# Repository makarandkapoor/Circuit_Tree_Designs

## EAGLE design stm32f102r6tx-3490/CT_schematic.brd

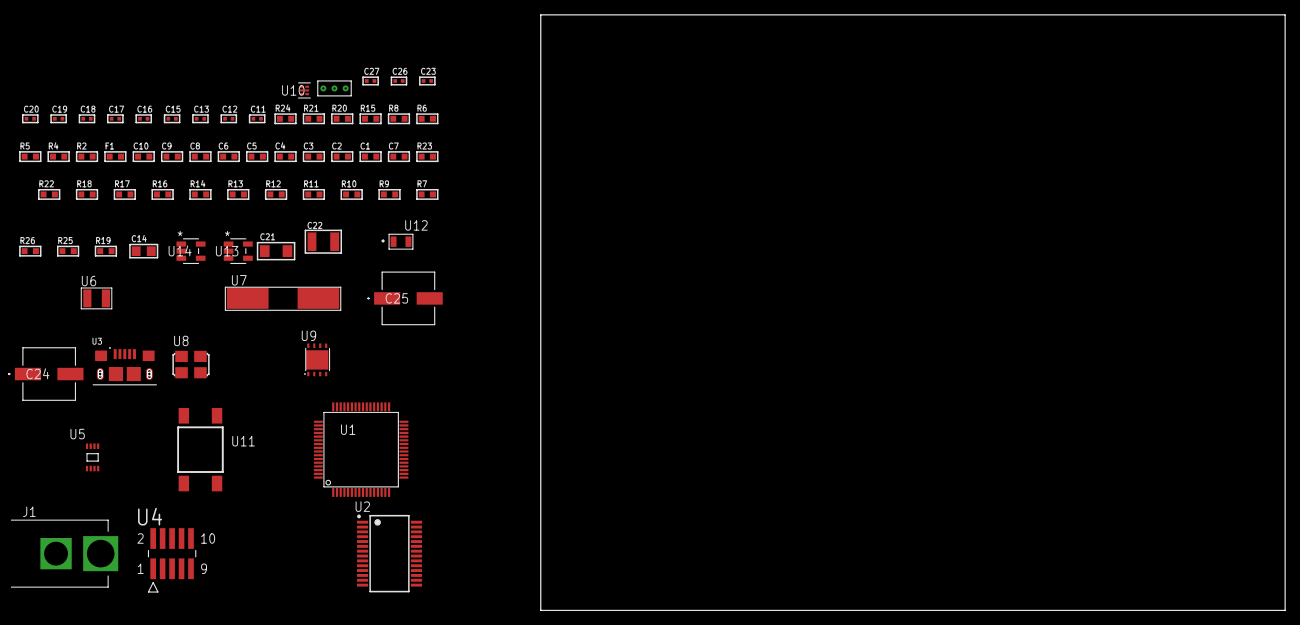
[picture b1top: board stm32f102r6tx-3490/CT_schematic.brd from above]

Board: 2 copper layers, 159.4 x 80.0 mm, 68 parts (0 on the bottom side), 42 nets, no tracks yet.

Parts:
C1, C10: 1e-06; C0603
C2, C3, C4, C5, C6: 1e-07; C0603
C7: 4.7e-06; C0603
C8, C9: 1e-08; C0603
C11, C12: 1e-11; C0402
C13, C15, C16, C17, C23: 1e-07; C0402
C14: 4.7e-06; C0805
C18, C19, C20, C26, C27: 1e-08; C0402
C21: 1e-05; C1206
C22: 1e-05; C1210
C24, C25: 0.0001; EXV-9H
F1: 240.0; L0603
J1: PJ-037B; PJ-037B_PACKAGE
R2, R21: 1000.0; R0603
R4, R8: 4700.0; R0603
R5, R6: 2200.0; R0603
R7, R9, R10, R11, R12, R13, R14, R16, R17, R18, R22, R23: 10000.0; R0603
R15: 5.0; R0603
R19: 100000.0; R0603
R20: 2231.0; R0603
R24: 9100.0; R0603
R25: 680000.0; R0603
R26: 120000.0; R0603
U1: STM32F102R6T6; LQFP64
U2: FT232RL-REEL; SSOP-28
U3: 10118193-0001LF; FCI_10118193-0001LF
U4: FTSH-105-01-L-DV-K; SAMTEC_FTSH-105-01-L-DV-K
U5: 24AA64T-I/MNY; TDFN-8/6MM
U6: ABS07-32.768KHZ-7-T
U7: ABLS-12.000MHZ-B4-T
U8: ASFL1-25MHZ-NCS; ASFL1
U9: LP3878SDX-ADJ/NOPB; WSON-8
U10: TPS3895ADRYR; SON-6
U11: 4-1437565-2; SW_4-1437565-2
U12: Q65110A2395; LGM67K-G1J2-24-Z
U13, U14: nc7sz125m5x; NC7SZ125M5X
U15: Dummy; DUMMY_PACKAGE_146

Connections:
CLK_CRYSTAL_U1_3: C11.1, U1.3, U6.1
CLK_CRYSTAL_U1_4: C12.1, U1.4, U6.2
CLK_CRYSTAL_U2_27: U2.27, U7.1
CLK_CRYSTAL_U2_28: U2.28, U7.2
CLK_U1_5: U1.5, U8.3
GND: C1.2, C2.2, C3.2, C4.2, C5.2, C6.2, C7.2, C8.2, C9.2, C10.2, C11.2, C12.2, C13.2, C14.2, C15.2, C16.2, C17.2, C18.2, C19.2, C20.2, C21.2, C22.2, C23.2, C24.2, C25.2, C26.2, C27.2, J1.2, R2.2, R7.2, R10.2, R14.2, R15.2, R16.2, R17.2, R21.2, R24.2, R26.2, U1.12, U1.18, U1.31, U1.47, U1.63, U2.7, U2.18, U2.21, U2.25, U2.26, U3.5, U3.6, U3.7, U3.8, U3.9, U4.3, U4.5, U5.4, U8.2, U9.3, U9.PAD, U10.2, U12.C, U13.2, U13.3, U14.1, U14.3, U15.1
NET_U1_7: R4.1, U1.7, U14.4
NET_U1_13: C8.1, C9.1, C10.1, F1.1, U1.13
NET_U1_58: R5.1, U1.58, U5.6
NET_U1_59: R6.1, U1.59, U5.5
NET_U1_60: R7.1, U1.60
NET_U1_62: U11.3, U11.4
NET_U2_14: R9.1, U2.14
NET_U2_17: C15.1, U2.17
NET_U2_19: R10.1, U2.19
NET_U3_1: R8.1, U3.1
NET_U3_2: U2.16, U3.2
NET_U3_3: U2.15, U3.3
NET_U4_2: R13.1, U4.2
NET_U4_4: R14.1, U4.4
NET_U4_9: R15.1, U4.9
NET_U5_1: R16.1, U5.1
NET_U5_2: R17.1, U5.2
NET_U5_3: R18.1, U5.3
NET_U9_1: C20.1, U9.1
NET_U9_6: R20.2, R21.1, U9.6
NET_U9_8: R19.1, U9.8
NET_U10_1: R23.1, R24.1, U10.1
NET_U10_3: R25.2, R26.1, U10.3
NET_U10_4: R22.1, U10.4, U13.4, U14.2
NET_U11_1: R2.1, U11.1, U11.2
PROC_SYS_JTDI: R12.1, U1.50, U4.8
PROC_SYS_JTDO_TRACESWO: U1.55, U4.6
PROC_TIM2_CH3: U1.16, U15.3
PROC_TIM2_CH4: U1.17, U15.2
PROC_USART1_CTS: U1.44, U2.3
PROC_USART1_RTS: U1.45, U2.11
PROC_USART1_RX: U1.43, U2.1
PROC_USART1_TX: U1.42, U2.5
RST_OUT_U4_JTAG_RST_B: R11.1, U4.10, U13.1
VCC_S1_6V0: C21.1, C24.1, C25.1, J1.1, R19.2, U9.4
VCC_TIER1_3V3: C1.1, C2.1, C3.1, C4.1, C5.1, C6.1, C7.1, C13.1, C14.1, C16.1, C17.1, C18.1, C19.1, C22.1, C23.1, C26.1, C27.1, F1.2, R4.2, R5.2, R6.2, R9.2, R11.2, R12.2, R13.2, R18.2, R20.1, R22.2, R23.2, R25.1, U1.1, U1.19, U1.32, U1.48, U1.64, U2.4, U2.20, U4.1, U5.7, U5.8, U8.4, U9.5, U10.6, U13.5, U14.5

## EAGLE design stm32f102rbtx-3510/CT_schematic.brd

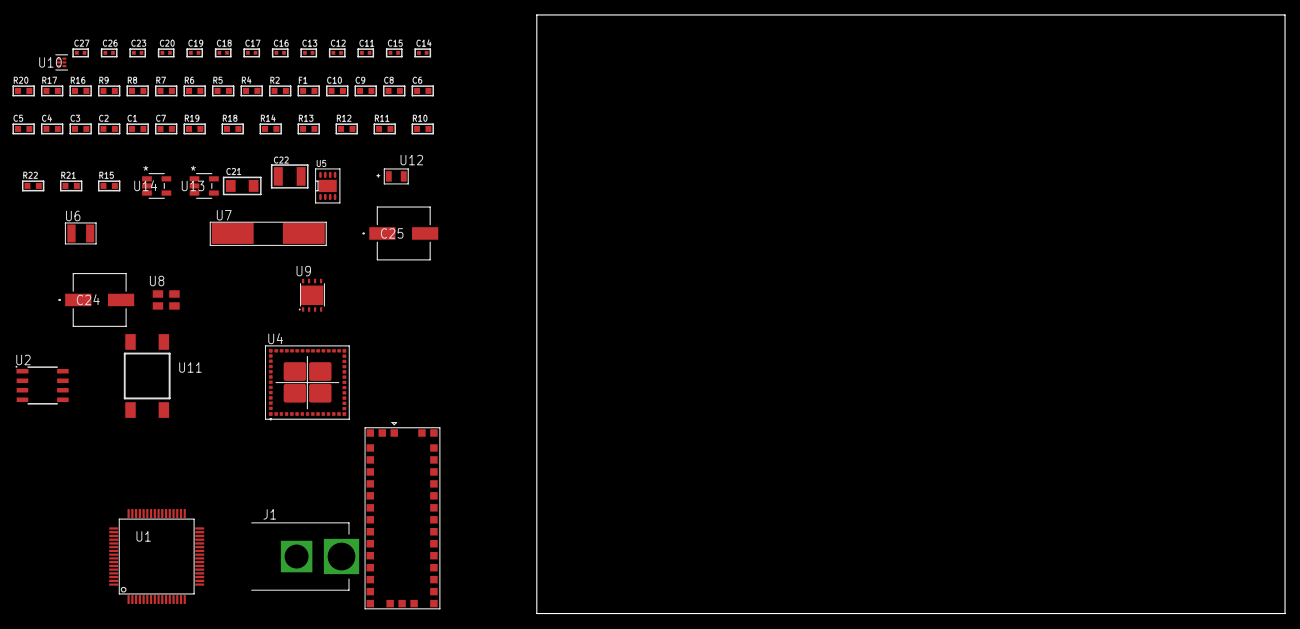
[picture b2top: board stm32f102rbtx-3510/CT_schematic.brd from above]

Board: 2 copper layers, 100.0 x 80.0 mm, 63 parts (0 on the bottom side), 35 nets, no tracks yet.

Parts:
C1, C10: 1e-06; C0603
C2, C3, C4, C5, C6: 1e-07; C0603
C7: 4.7e-06; C0603
C8, C9: 1e-08; C0603
C11, C12: 1e-11; C0402
C13, C19, C20, C26, C27: 1e-08; C0402
C14, C15: 2.2e-11; C0402
C16, C17, C18, C23: 1e-07; C0402
C21: 1e-05; C1206
C22: 1e-05; C1210
C24, C25: 0.0001; EXV-9H
F1: 240.0; L0603
J1: PJ-037B; PJ-037B_PACKAGE
R2, R17: 1000.0; R0603
R4, R5: 4700.0; R0603
R6, R7, R8, R9: 2200.0; R0603
R10, R11, R12, R13, R14, R18, R19: 10000.0; R0603
R15: 100000.0; R0603
R16: 2231.0; R0603
R20: 9100.0; R0603
R21: 680000.0; R0603
R22: 120000.0; R0603
U1: STM32F102RBT6; LQFP64
U2: AT25512N-SH-T; SOIC-8
U3: M10382
U4: MBH7BLZ02-109004
U5: PCF85063TP/1Z; SON-8
U6: ABS07-32.768KHZ-7-T
U7: ABLS-25.000MHZ-B2F-T
U8: ASEK-32.768KHz-ECST; ASEK
U9: LP3878SDX-ADJ/NOPB; WSON-8
U10: TPS3895ADRYR; SON-6
U11: 4-1437565-2; SW_4-1437565-2
U12: Q65110A2395; LGM67K-G1J2-24-Z
U13, U14: nc7sz125m5x; NC7SZ125M5X

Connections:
CLK_CRYSTAL_U1_5: C11.1, U1.5, U7.1
CLK_CRYSTAL_U1_6: C12.1, U1.6, U7.2
CLK_CRYSTAL_U5_1: U5.1, U6.1
CLK_CRYSTAL_U5_2: U5.2, U6.2
CLK_U1_3: U1.3, U8.3
GND: C1.2, C2.2, C3.2, C4.2, C5.2, C6.2, C7.2, C8.2, C9.2, C10.2, C11.2, C12.2, C13.2, C14.2, C15.2, C16.2, C17.2, C18.2, C19.2, C20.2, C21.2, C22.2, C23.2, C24.2, C25.2, C26.2, C27.2, J1.2, R2.2, R10.2, R17.2, R20.2, R22.2, U1.12, U1.18, U1.31, U1.47, U1.63, U2.4, U3.2, U3.4, U3.14, U3.17, U3.21, U3.24, U3.26, U3.28, U3.33, U3.34, U3.35, U3.36, U4.1, U4.3, U4.15, U4.27, U4.29, U4.41, U4.42, U4.43, U4.44, U4.45, U4.46, U4.47, U4.48, U4.49, U4.50, U4.52, U4.53, U4.54, U4.55, U4.56, U5.4, U5.PAD, U8.2, U9.3, U9.PAD, U10.2, U12.C, U13.1, U13.3, U14.1, U14.3
NET_U1_7: R5.1, U1.7, U14.4
NET_U1_13: C8.1, C9.1, C10.1, F1.1, U1.13
NET_U1_29: R8.1, U1.29, U5.6
NET_U1_30: R9.1, U1.30, U5.5
NET_U1_58: R6.1, U1.58, U3.19
NET_U1_59: R7.1, U1.59, U3.18
NET_U1_60: R10.1, U1.60
NET_U1_62: U11.3, U11.4
NET_U2_3: R11.1, U2.3
NET_U2_7: R13.1, U2.7
NET_U4_39: R4.1, U4.39, U13.4
NET_U5_3: R14.1, U5.3
NET_U9_1: C20.1, U9.1
NET_U9_6: R16.2, R17.1, U9.6
NET_U9_8: R15.1, U9.8
NET_U10_1: R19.1, R20.1, U10.1
NET_U10_3: R21.2, R22.1, U10.3
NET_U10_4: R18.1, U10.4, U13.2, U14.2
NET_U11_1: R2.1, U11.1, U11.2
PROC_SPI1_MISO: U1.22, U2.2
PROC_SPI1_MOSI: U1.23, U2.5
PROC_SPI1_NSS: R12.1, U1.20, U2.1
PROC_SPI1_SCK: U1.21, U2.6
PROC_USART1_CTS: U1.44, U4.26
PROC_USART1_RTS: U1.45, U4.24
PROC_USART1_RX: U1.43, U4.25
PROC_USART1_TX: U1.42, U4.23
VCC_S1_9V8: C21.1, C24.1, C25.1, J1.1, R15.2, U9.4
VCC_TIER1_3V3: C1.1, C2.1, C3.1, C4.1, C5.1, C6.1, C7.1, C13.1, C14.1, C15.1, C16.1, C17.1, C18.1, C19.1, C22.1, C23.1, C26.1, C27.1, F1.2, R4.2, R5.2, R6.2, R7.2, R8.2, R9.2, R11.2, R12.2, R13.2, R14.2, R16.1, R18.2, R19.2, R21.1, U1.1, U1.19, U1.32, U1.48, U1.64, U2.8, U3.5, U3.25, U3.27, U4.28, U5.8, U8.4, U9.5, U10.6, U13.5, U14.5

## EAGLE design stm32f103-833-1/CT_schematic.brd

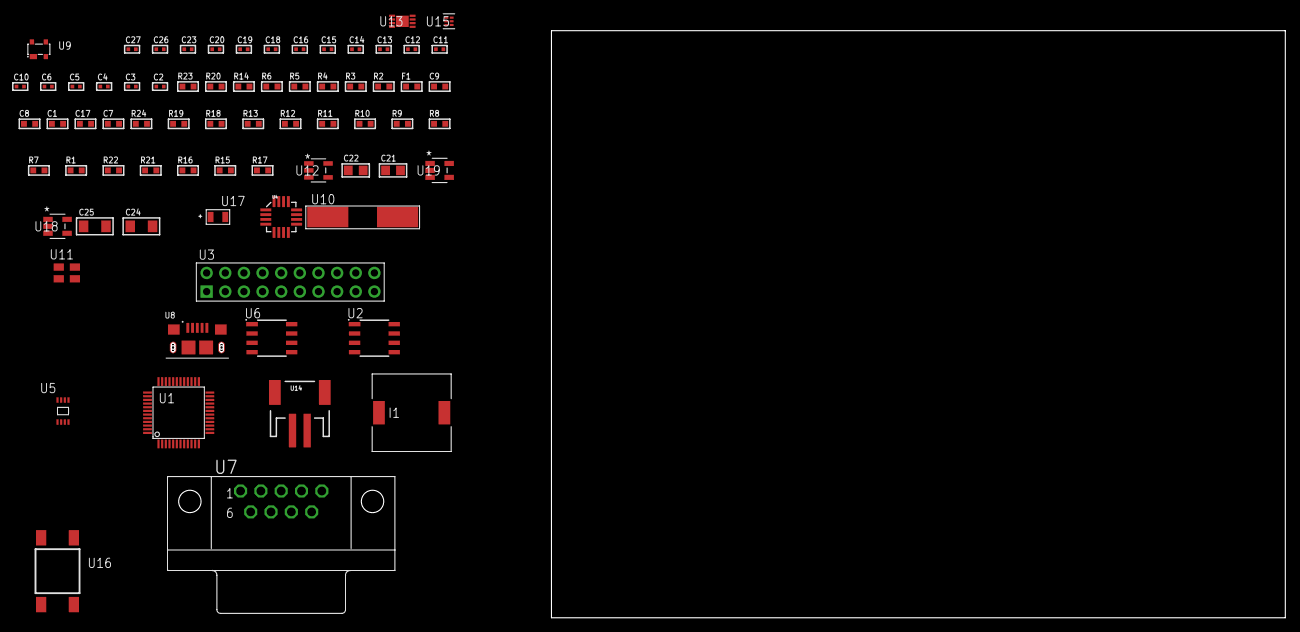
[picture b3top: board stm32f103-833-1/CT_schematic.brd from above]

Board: 2 copper layers, 72 parts (0 on the bottom side), 46 nets, no tracks yet.

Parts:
C1, C9: 1e-06; C0603
C2, C3, C4, C5, C6, C13, C19, C23: 1e-07; C0402
C7: 4.7e-06; C0603
C8: 1e-08; C0603
C10, C11: 1e-11; C0402
C12, C14, C15, C16, C18, C20, C26, C27: 1e-08; C0402
C17: 4.7e-07; C0603
C21, C22: 1e-05; C0805
C24, C25: 1e-05; C1206
F1: 600.0; L0603
I1: 3.8e-06; DR1040
R1, R7, R8, R9, R10, R11, R12, R13, R18, R19, R24: 10000.0; R0603
R2: 1000.0; R0603
R3: 1600.5; R0603
R4: 4700.0; R0603
R5, R6: 2200.0; R0603
R14: 120.0; R0603
R15: 470000.0; R0603
R16: 220000.0; R0603
R17: 1000000.0; R0603
R20: 9100.0; R0603
R21: 680000.0; R0603
R22: 120000.0; R0603
R23: 2000.0; R0603
U1: STM32F103C4T6; LQFP48
U2: AT25256B-SSHL-T; SOIC-8
U3: TST-110-05-T-D-RA
U4: l3g4200d; LGA-16
U5: 24AA08T-I/MNY; TDFN-8/6MM
U6: SN65HVD230D; SOIC-8
U7: 182-009-113R531; 182-009-MALE
U8: 10118193-0001LF; FCI_10118193-0001LF
U9: prtr5v0u2ax; SOT143B
U10: ABLS-25.000MHZ-B2F-T
U11: ASEK-32.768KHz-ECST; ASEK
U12: ltc3406es5; TSOT-23-5
U13: MCP73831T-2ACI/MC; DFN8_2X3MC
U14: S2B-PH-SM4-TB(LF)(SN); JST-2-SMD
U15: TPS3895ADRYR; SON-6
U16: 4-1437565-2; SW_4-1437565-2
U17: Q65110A2395; LGM67K-G1J2-24-Z
U18, U19: nc7sz125m5x; NC7SZ125M5X

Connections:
CLK_CRYSTAL_U1_5: C10.1, U1.5, U10.1
CLK_CRYSTAL_U1_6: C11.1, U1.6, U10.2
CLK_U1_3: U1.3, U11.3
GND: C1.2, C2.2, C3.2, C4.2, C5.2, C6.2, C7.2, C8.2, C9.2, C10.2, C11.2, C12.2, C13.2, C14.2, C15.2, C16.2, C18.2, C19.2, C20.2, C21.2, C22.1, C22.2, C23.2, C24.2, C25.2, C26.2, C27.2, R2.2, R7.2, R12.1, R12.2, R15.2, R16.2, R20.2, R22.2, R23.2, U1.23, U1.35, U1.47, U2.4, U3.4, U3.6, U3.8, U3.10, U3.12, U3.14, U3.16, U3.18, U3.20, U4.8, U4.9, U4.10, U4.11, U4.12, U4.13, U5.4, U5.7, U6.2, U7.5, U8.5, U8.6, U8.7, U8.8, U8.9, U9.1, U11.2, U12.2, U13.6, U13.9, U14.2, U15.2, U17.C, U18.2, U18.3, U19.1, U19.3
INPUT_USBPOWER_5V: C24.1, R24.2, U8.1, U9.4, U13.1, U13.2
NET_U1_7: R4.1, U1.7, U19.4
NET_U1_8: C2.1, U1.8
NET_U1_9: C8.1, C9.1, F1.1, U1.9
NET_U1_40: R3.1, U1.40, U17.A
NET_U1_41: R1.1, U1.41, U16.3, U16.4
NET_U1_42: R5.1, U1.42, U5.6
NET_U1_43: R6.1, U1.43, U5.5
NET_U1_44: R7.1, U1.44
NET_U2_3: R8.1, U2.3
NET_U2_7: R10.1, U2.7
NET_U4_14: C16.1, C17.1, U4.14
NET_U6_6: R14.2, U6.6
NET_U6_8: R15.1, U6.8
NET_U7_2: R14.2, U6.6, U7.2
NET_U7_3: R14.1, U6.7, U7.3
NET_U12_3: I1.1, U12.3
NET_U12_5: R16.1, R17.1, U12.5
NET_U12_ATNET_3: I1.2, R17.2
NET_U13_5: R24.1, U13.5
NET_U13_8: R23.1, U13.8
NET_U15_1: R19.1, R20.1, U15.1
NET_U15_3: R21.2, R22.1, U15.3
NET_U15_4: R18.1, U15.4, U18.4, U19.2
NET_U16_1: R2.1, U16.1, U16.2
PROC_CAN_RX: U1.45, U6.4
PROC_CAN_TX: U1.46, U6.1
PROC_SPI1_MISO: U1.16, U4.4
PROC_SPI1_MOSI: U1.17, U4.3
PROC_SPI1_NSS: R9.1, R13.1, U1.14, U1.38, U2.1, U4.5
PROC_SPI1_SCK: U1.15, U4.2
PROC_SPI2_MISO: U1.27, U2.2
PROC_SPI2_MOSI: U1.28, U2.5
PROC_SPI2_SCK: U1.26, U2.6
PROC_SYS_JTCK_SWCLK: U1.37, U3.9
PROC_SYS_JTDO_TRACESWO: U1.39, U3.13
PROC_SYS_JTMS_SWDIO: U1.34, U3.7
PROC_USB_DM: U1.32, U8.2, U9.3
PROC_USB_DP: U1.33, U8.3, U9.2
RST_OUT_U3_SRESET_B: R11.1, U3.15, U18.1
VCC_S1_3V7: C21.1, C25.1, U12.4, U13.3, U13.4, U14.1
VCC_TIER1_3V3: C1.1, C3.1, C4.1, C5.1, C6.1, C7.1, C12.1, C13.1, C14.1, C15.1, C18.1, C19.1, C20.1, C22.2, C23.1, C26.1, C27.1, F1.2, I1.2, R1.2, R3.2, R4.2, R5.2, R6.2, R8.2, R9.2, R10.2, R11.2, R13.2, R17.2, R18.2, R19.2, R21.1, U1.1, U1.24, U1.36, U1.48, U2.8, U3.1, U4.1, U4.15, U4.16, U5.8, U6.3, U11.4, U15.6, U18.5, U19.5

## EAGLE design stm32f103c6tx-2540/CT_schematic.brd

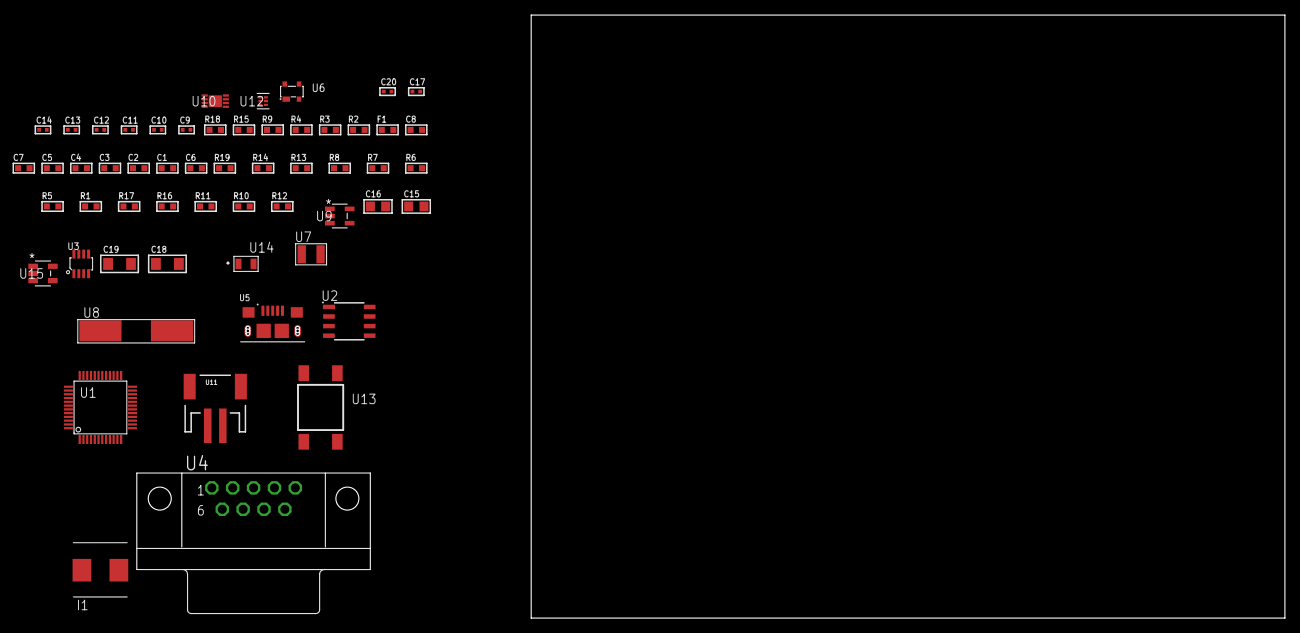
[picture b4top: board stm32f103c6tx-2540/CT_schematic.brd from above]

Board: 2 copper layers, 56 parts (0 on the bottom side), 36 nets, no tracks yet.

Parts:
C1, C8: 1e-06; C0603
C2, C3, C4, C5: 1e-07; C0603
C6: 4.7e-06; C0603
C7: 1e-08; C0603
C9, C10, C11, C12: 1e-11; C0402
C13, C20: 1e-08; C0402
C14, C17: 1e-07; C0402
C15, C16: 1e-05; C0805
C18, C19: 1e-05; C1206
F1: 240.0; L0603
I1: 2e-06; WE-HCI_7030/7040/7050
R1, R5, R6, R7, R8, R13, R14, R19: 10000.0; R0603
R2: 1000.0; R0603
R3: 1600.5; R0603
R4: 4700.0; R0603
R9: 120.0; R0603
R10: 100000.0; R0603
R11: 220000.0; R0603
R12: 1000000.0; R0603
R15: 9100.0; R0603
R16: 680000.0; R0603
R17: 120000.0; R0603
R18: 2000.0; R0603
U1: stm32f103c6t7; LQFP48
U2: AT25320B-SSHL-T; SOIC-8
U3: MAX3051EKA+T; SOT-23-8
U4: 182-009-113R531; 182-009-MALE
U5: 10118193-0001LF; FCI_10118193-0001LF
U6: prtr5v0u2ax; SOT143B
U7: ABS07-32.768KHZ-7-T
U8: ABLS-25.000MHZ-B2F-T
U9: ltc3406es5; TSOT-23-5
U10: MCP73831T-2ACI/MC; DFN8_2X3MC
U11: S2B-PH-SM4-TB(LF)(SN); JST-2-SMD
U12: TPS3895ADRYR; SON-6
U13: 4-1437565-2; SW_4-1437565-2
U14: Q65110A2395; LGM67K-G1J2-24-Z
U15: nc7sz125m5x; NC7SZ125M5X

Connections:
CLK_CRYSTAL_U1_3: C9.1, U1.3, U7.1
CLK_CRYSTAL_U1_4: C10.1, U1.4, U7.2
CLK_CRYSTAL_U1_5: C11.1, U1.5, U8.1
CLK_CRYSTAL_U1_6: C12.1, U1.6, U8.2
GND: C1.2, C2.2, C3.2, C4.2, C5.2, C6.2, C7.2, C8.2, C9.2, C10.2, C11.2, C12.2, C13.2, C14.2, C15.2, C16.1, C16.2, C17.2, C18.2, C19.2, C20.2, R2.2, R5.2, R10.2, R11.2, R15.2, R17.2, R18.2, U1.8, U1.23, U1.35, U1.47, U2.4, U3.2, U4.5, U5.5, U5.6, U5.7, U5.8, U5.9, U6.1, U9.2, U10.6, U10.9, U11.2, U12.2, U14.C, U15.1, U15.3
INPUT_USBPOWER_5V: C18.1, R19.2, U5.1, U6.4, U10.1, U10.2
NET_U1_7: R4.1, U1.7, U15.4
NET_U1_9: C7.1, C8.1, F1.1, U1.9
NET_U1_42: R3.1, U1.42, U14.A
NET_U1_43: R1.1, U1.43, U13.3, U13.4
NET_U1_44: R5.1, U1.44
NET_U2_3: R6.1, U2.3
NET_U2_7: R8.1, U2.7
NET_U3_6: R9.2, U3.6
NET_U3_8: R10.1, U3.8
NET_U4_2: R9.2, U3.6, U4.2
NET_U4_3: R9.1, U3.7, U4.3
NET_U9_3: I1.1, U9.3
NET_U9_5: R11.1, R12.1, U9.5
NET_U9_ATNET_3: I1.2, R12.2
NET_U10_5: R19.1, U10.5
NET_U10_8: R18.1, U10.8
NET_U12_1: R14.1, R15.1, U12.1
NET_U12_3: R16.2, R17.1, U12.3
NET_U12_4: R13.1, U12.4, U15.2
NET_U13_1: R2.1, U13.1, U13.2
PROC_CAN_RX: U1.45, U3.4
PROC_CAN_TX: U1.46, U3.1
PROC_SPI1_MISO: U1.16, U2.2
PROC_SPI1_MOSI: U1.17, U2.5
PROC_SPI1_NSS: R7.1, U1.14, U2.1
PROC_SPI1_SCK: U1.15, U2.6
PROC_USB_DM: U1.32, U5.2, U6.3
PROC_USB_DP: U1.33, U5.3, U6.2
VCC_S1_3V7: C15.1, C19.1, U9.4, U10.3, U10.4, U11.1
VCC_TIER1_3V3: C1.1, C2.1, C3.1, C4.1, C5.1, C6.1, C13.1, C14.1, C16.2, C17.1, C20.1, F1.2, I1.2, R1.2, R3.2, R4.2, R6.2, R7.2, R8.2, R12.2, R13.2, R14.2, R16.1, U1.1, U1.24, U1.36, U1.48, U2.8, U3.3, U12.6, U15.5

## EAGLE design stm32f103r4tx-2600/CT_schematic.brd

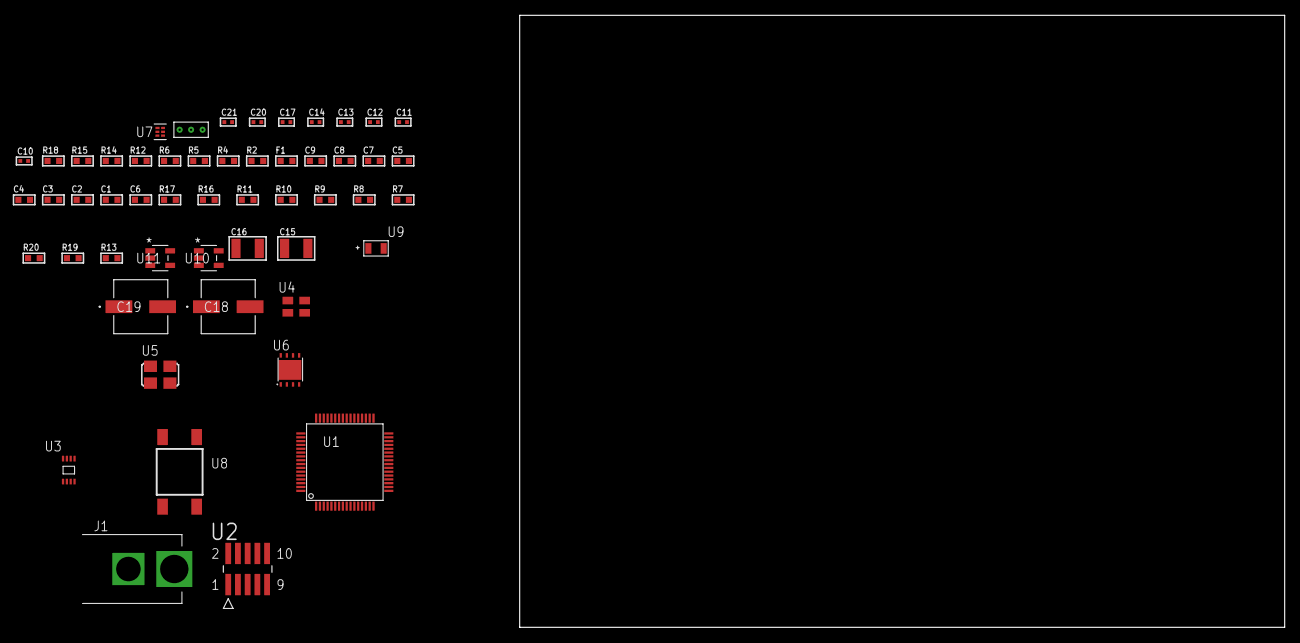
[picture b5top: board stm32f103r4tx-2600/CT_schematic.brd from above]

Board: 2 copper layers, 100.0 x 80.0 mm, 53 parts (0 on the bottom side), 26 nets, no tracks yet.

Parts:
C1, C9: 1e-06; C0603
C2, C3, C4, C5, C7: 1e-07; C0603
C6: 4.7e-06; C0603
C8: 1e-08; C0603
C10, C17: 1e-07; C0402
C11, C12, C13, C14, C20, C21: 1e-08; C0402
C15, C16: 1e-05; C1210
C18, C19: 0.0001; EXV-9H
F1: 240.0; L0603
J1: PJ-037B; PJ-037B_PACKAGE
R2, R15: 1000.0; R0603
R4: 4700.0; R0603
R5, R6: 2200.0; R0603
R7, R8, R9, R10, R11, R16, R17: 10000.0; R0603
R12: 5.0; R0603
R13: 100000.0; R0603
R14: 2231.0; R0603
R18: 9100.0; R0603
R19: 680000.0; R0603
R20: 120000.0; R0603
U1: stm32f103r4t6; LQFP64
U2: FTSH-105-01-L-DV-K; SAMTEC_FTSH-105-01-L-DV-K
U3: 24AA00T-I/MNY; TDFN-8/6MM
U4: ASEK-32.768KHz-ECST; ASEK
U5: ASFL1-25MHZ-NCS; ASFL1
U6: LP3878SDX-ADJ/NOPB; WSON-8
U7: TPS3895ADRYR; SON-6
U8: 4-1437565-2; SW_4-1437565-2
U9: Q65110A2395; LGM67K-G1J2-24-Z
U10, U11: nc7sz125m5x; NC7SZ125M5X
U12: Dummy; DUMMY_PACKAGE_115

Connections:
CLK_U1_3: U1.3, U4.3
CLK_U1_5: U1.5, U5.3
GND: C1.2, C2.2, C3.2, C4.2, C5.2, C6.2, C7.2, C8.2, C9.2, C10.2, C11.2, C12.2, C13.2, C14.2, C15.2, C16.2, C17.2, C18.2, C19.2, C20.2, C21.2, J1.2, R2.2, R7.2, R11.2, R12.2, R15.2, R18.2, R20.2, U1.12, U1.18, U1.31, U1.47, U1.63, U2.3, U2.5, U3.4, U4.2, U5.2, U6.3, U6.PAD, U7.2, U9.C, U10.2, U10.3, U11.1, U11.3, U12.1
NET_U1_7: R4.1, U1.7, U11.4
NET_U1_13: C8.1, C9.1, F1.1, U1.13
NET_U1_58: R5.1, U1.58, U3.6
NET_U1_59: R6.1, U1.59, U3.5
NET_U1_60: R7.1, U1.60
NET_U1_62: U8.3, U8.4
NET_U2_2: R10.1, U2.2
NET_U2_4: R11.1, U2.4
NET_U2_9: R12.1, U2.9
NET_U6_1: C14.1, U6.1
NET_U6_6: R14.2, R15.1, U6.6
NET_U6_8: R13.1, U6.8
NET_U7_1: R17.1, R18.1, U7.1
NET_U7_3: R19.2, R20.1, U7.3
NET_U7_4: R16.1, U7.4, U10.4, U11.2
NET_U8_1: R2.1, U8.1, U8.2
PROC_ADC1_IN3: U1.17, U12.3
PROC_ADC1_IN4: U1.20, U12.2
PROC_SYS_JTDI: R9.1, U1.50, U2.8
PROC_SYS_JTDO_TRACESWO: U1.55, U2.6
RST_OUT_U2_JTAG_RST_B: R8.1, U2.10, U10.1
VCC_S1_12V8: C15.1, C18.1, C19.1, J1.1, R13.2, U6.4
VCC_TIER1_3V3: C1.1, C2.1, C3.1, C4.1, C5.1, C6.1, C7.1, C10.1, C11.1, C12.1, C13.1, C16.1, C17.1, C20.1, C21.1, F1.2, R4.2, R5.2, R6.2, R8.2, R9.2, R10.2, R14.1, R16.2, R17.2, R19.1, U1.1, U1.19, U1.32, U1.48, U1.64, U2.1, U3.8, U4.4, U5.4, U6.5, U7.6, U10.5, U11.5

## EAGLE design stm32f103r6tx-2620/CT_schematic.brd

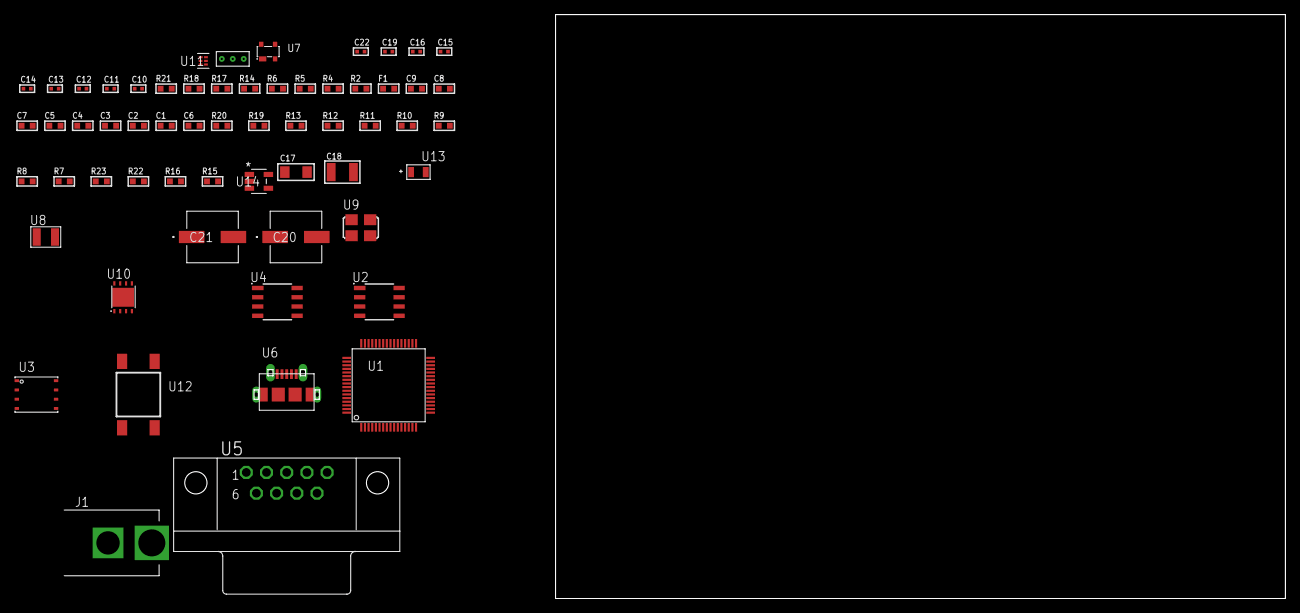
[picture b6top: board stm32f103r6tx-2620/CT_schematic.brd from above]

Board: 2 copper layers, 60 parts (0 on the bottom side), 39 nets, no tracks yet.

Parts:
C1, C9: 1e-06; C0603
C2, C3, C4, C5, C7: 1e-07; C0603
C6: 4.7e-06; C0603
C8: 1e-08; C0603
C10, C11: 1e-11; C0402
C12, C13, C15, C16, C22: 1e-08; C0402
C14, C19: 1e-07; C0402
C17: 1e-05; C1206
C18: 1e-05; C1210
C20, C21: 0.0001; EXV-9H
F1: 240.0; L0603
J1: PJ-037B; PJ-037B_PACKAGE
R2, R18: 1000.0; R0603
R4: 4700.0; R0603
R5, R6: 2200.0; R0603
R7, R8, R9, R10, R11, R12, R13, R19, R20: 10000.0; R0603
R14: 120.0; R0603
R15, R16: 100000.0; R0603
R17: 2231.0; R0603
R21: 9100.0; R0603
R22: 680000.0; R0603
R23: 120000.0; R0603
U1: stm32f103r6t7; LQFP64
U2: AT25128B-SSHL-T; SOIC-8
U3: 24AA512-I/MF; DFN8-S
U4: SN65HVD230D; SOIC-8
U5: 182-009-113R531; 182-009-MALE
U6: 47590-0001; MICRO_USB_AB
U7: prtr5v0u2ax; SOT143B
U8: ABS07-32.768KHZ-7-T
U9: ASFL1-25MHZ-NCS; ASFL1
U10: LP3878SDX-ADJ/NOPB; WSON-8
U11: TPS3895ADRYR; SON-6
U12: 4-1437565-2; SW_4-1437565-2
U13: Q65110A2395; LGM67K-G1J2-24-Z
U14: nc7sz125m5x; NC7SZ125M5X
U15: Dummy; DUMMY_PACKAGE_131

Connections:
CLK_CRYSTAL_U1_3: C10.1, U1.3, U8.1
CLK_CRYSTAL_U1_4: C11.1, U1.4, U8.2
CLK_U1_5: U1.5, U9.3
GND: C1.2, C2.2, C3.2, C4.2, C5.2, C6.2, C7.2, C8.2, C9.2, C10.2, C11.2, C12.2, C13.2, C14.2, C15.2, C16.2, C17.2, C18.2, C19.2, C20.2, C21.2, C22.2, J1.2, R2.2, R7.2, R11.2, R12.2, R15.2, R18.2, R21.2, R23.2, U1.12, U1.18, U1.31, U1.47, U1.63, U2.4, U3.4, U4.2, U5.5, U6.5, U6.6, U6.7, U6.8, U6.9, U7.1, U9.2, U10.3, U10.PAD, U11.2, U13.C, U14.1, U14.3, U15.1
NET_U1_7: R4.1, U1.7, U14.4
NET_U1_13: C8.1, C9.1, F1.1, U1.13
NET_U1_57: U12.3, U12.4
NET_U1_58: R5.1, U1.58, U3.6
NET_U1_59: R6.1, U1.59, U3.5
NET_U1_60: R7.1, U1.60
NET_U2_3: R8.1, U2.3
NET_U2_7: R10.1, U2.7
NET_U3_1: R11.1, U3.1
NET_U3_2: R12.1, U3.2
NET_U3_3: R13.1, U3.3
NET_U4_6: R14.2, U4.6
NET_U4_8: R15.1, U4.8
NET_U5_2: R14.2, U4.6, U5.2
NET_U5_3: R14.1, U4.7, U5.3
NET_U7_4: U6.1, U7.4
NET_U10_1: C16.1, U10.1
NET_U10_6: R17.2, R18.1, U10.6
NET_U10_8: R16.1, U10.8
NET_U11_1: R20.1, R21.1, U11.1
NET_U11_3: R22.2, R23.1, U11.3
NET_U11_4: R19.1, U11.4, U14.2
NET_U12_1: R2.1, U12.1, U12.2
PROC_ADC1_IN3: U1.17, U15.2
PROC_ADC1_IN14: U1.24, U15.3
PROC_CAN_RX: U1.61, U4.4
PROC_CAN_TX: U1.62, U4.1
PROC_SPI1_MISO: U1.22, U2.2
PROC_SPI1_MOSI: U1.23, U2.5
PROC_SPI1_NSS: R9.1, U1.20, U2.1
PROC_SPI1_SCK: U1.21, U2.6
PROC_USB_DM: U1.44, U6.2, U7.3
PROC_USB_DP: U1.45, U6.3, U7.2
VCC_S1_10V9: C17.1, C20.1, C21.1, J1.1, R16.2, U10.4
VCC_TIER1_3V3: C1.1, C2.1, C3.1, C4.1, C5.1, C6.1, C7.1, C12.1, C13.1, C14.1, C15.1, C18.1, C19.1, C22.1, F1.2, R4.2, R5.2, R6.2, R8.2, R9.2, R10.2, R13.2, R17.1, R19.2, R20.2, R22.1, U1.1, U1.19, U1.32, U1.48, U1.64, U2.8, U3.7, U3.8, U4.3, U9.4, U10.5, U11.6, U14.5

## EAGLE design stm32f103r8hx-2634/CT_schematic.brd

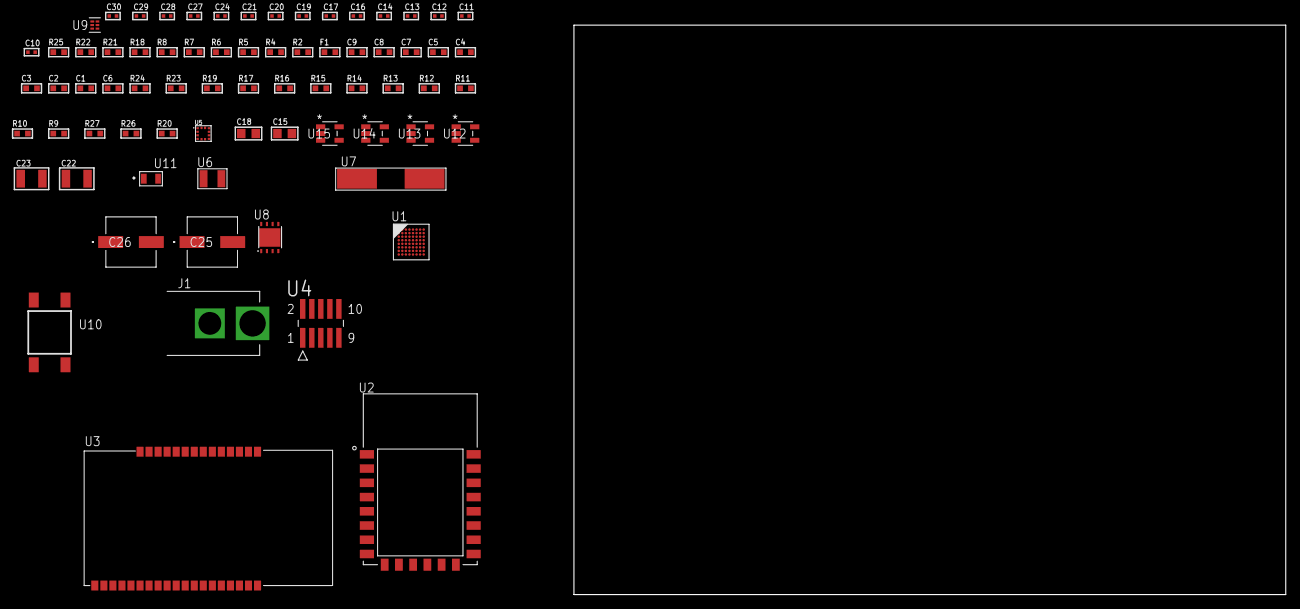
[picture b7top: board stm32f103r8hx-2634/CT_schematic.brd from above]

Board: 2 copper layers, 100.0 x 80.0 mm, 72 parts (0 on the bottom side), 40 nets, no tracks yet.

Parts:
C1, C9: 1e-06; C0603
C2, C3, C4, C5, C7: 1e-07; C0603
C6: 4.7e-06; C0603
C8: 1e-08; C0603
C10, C11, C12, C13: 1e-11; C0402
C14, C16, C17, C19, C20, C24: 1e-07; C0402
C15, C18: 1e-05; C0805
C21, C27, C28, C29, C30: 1e-08; C0402
C22, C23: 1e-05; C1210
C25, C26: 0.0001; EXV-9H
F1: 240.0; L0603
J1: PJ-037B; PJ-037B_PACKAGE
R2, R22: 1000.0; R0603
R4, R5, R6: 4700.0; R0603
R7, R8: 2200.0; R0603
R9, R10, R11, R12, R13, R14, R15, R16, R17, R19, R23, R24: 10000.0; R0603
R18: 5.0; R0603
R20: 100000.0; R0603
R21: 2231.0; R0603
R25: 9100.0; R0603
R26: 680000.0; R0603
R27: 120000.0; R0603
U1: stm32f103r8h7; TFBGA64
U2: ESP8266-12E
U3: ETRX3587
U4: FTSH-105-01-L-DV-K; SAMTEC_FTSH-105-01-L-DV-K
U5: LIS2HH12TR; LGA-12
U6: ABS07-32.768KHZ-7-T
U7: ABLS-25.000MHZ-B2F-T
U8: LP3878SDX-ADJ/NOPB; WSON-8
U9: TPS3895ADRYR; SON-6
U10: 4-1437565-2; SW_4-1437565-2
U11: Q65110A2395; LGM67K-G1J2-24-Z
U12, U13, U14, U15: nc7sz125m5x; NC7SZ125M5X

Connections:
CLK_CRYSTAL_U1_A1: C10.1, U1.A1, U6.1
CLK_CRYSTAL_U1_B1: C11.1, U1.B1, U6.2
CLK_CRYSTAL_U1_C1: C12.1, U1.C1, U7.1
CLK_CRYSTAL_U1_D1: C13.1, U1.D1, U7.2
GND: C1.2, C2.2, C3.2, C4.2, C5.2, C6.2, C7.2, C8.2, C9.2, C10.2, C11.2, C12.2, C13.2, C14.2, C15.2, C16.2, C17.2, C18.2, C19.2, C20.2, C21.2, C22.2, C23.2, C24.2, C25.2, C26.2, C27.2, C28.2, C29.2, C30.2, J1.2, R2.2, R9.2, R12.2, R13.2, R17.2, R18.2, R22.2, R25.2, R27.2, U1.C2, U1.D4, U1.D5, U1.D6, U1.F1, U2.15, U3.1, U3.13, U3.19, U3.20, U3.31, U3.33, U4.3, U4.5, U5.5, U5.6, U5.7, U5.8, U8.3, U8.PAD, U9.2, U11.C, U12.2, U12.3, U13.1, U13.3, U14.1, U14.3, U15.1, U15.3
NET_U1_A3: R8.1, U1.A3, U5.4
NET_U1_B3: R7.1, U1.B3, U5.1
NET_U1_B4: R9.1, U1.B4
NET_U1_E1: R6.1, U1.E1, U15.4
NET_U1_H1: C8.1, C9.1, F1.1, U1.G1, U1.H1
NET_U1_H8: U10.3, U10.4
NET_U2_1: R4.1, U2.1, U13.4
NET_U2_3: R10.1, U2.3
NET_U2_18: R11.1, U2.18
NET_U3_7: R5.1, U3.7, U14.4
NET_U3_21: R13.1, U3.21
NET_U4_2: R16.1, U4.2
NET_U4_4: R17.1, U4.4
NET_U4_9: R18.1, U4.9
NET_U5_2: R19.1, U5.2
NET_U8_1: C21.1, U8.1
NET_U8_6: R21.2, R22.1, U8.6
NET_U8_8: R20.1, U8.8
NET_U9_1: R24.1, R25.1, U9.1
NET_U9_3: R26.2, R27.1, U9.3
NET_U9_4: R23.1, U9.4, U12.4, U13.2, U14.2, U15.2
NET_U10_1: R2.1, U10.1, U10.2
PROC_SPI1_MISO: U1.A4, U2.6
PROC_SPI1_MOSI: U1.C4, U2.7
PROC_SPI1_NSS: R12.1, U1.H3, U2.16
PROC_SPI1_SCK: U1.F4, U2.5
PROC_SYS_JTDI: R15.1, U1.A6, U4.8
PROC_SYS_JTDO_TRACESWO: U1.A5, U4.6
PROC_USART1_CTS: U1.C8, U3.8
PROC_USART1_RTS: U1.B8, U3.6
PROC_USART1_RX: U1.C3, U3.17
PROC_USART1_TX: U1.C7, U3.18
RST_OUT_U4_JTAG_RST_B: R14.1, U4.10, U12.1
VCC_S1_12V1: C22.1, C25.1, C26.1, J1.1, R20.2, U8.4
VCC_TIER1_3V3: C1.1, C2.1, C3.1, C4.1, C5.1, C6.1, C7.1, C14.1, C15.1, C16.1, C17.1, C18.1, C19.1, C20.1, C23.1, C24.1, C27.1, C28.1, C29.1, C30.1, F1.2, R4.2, R5.2, R6.2, R7.2, R8.2, R10.2, R11.2, R14.2, R15.2, R16.2, R19.2, R21.1, R23.2, R24.2, R26.1, U1.B2, U1.D2, U1.E4, U1.E5, U1.E6, U2.8, U3.32, U4.1, U5.9, U5.10, U8.5, U9.6, U12.5, U13.5, U14.5, U15.5

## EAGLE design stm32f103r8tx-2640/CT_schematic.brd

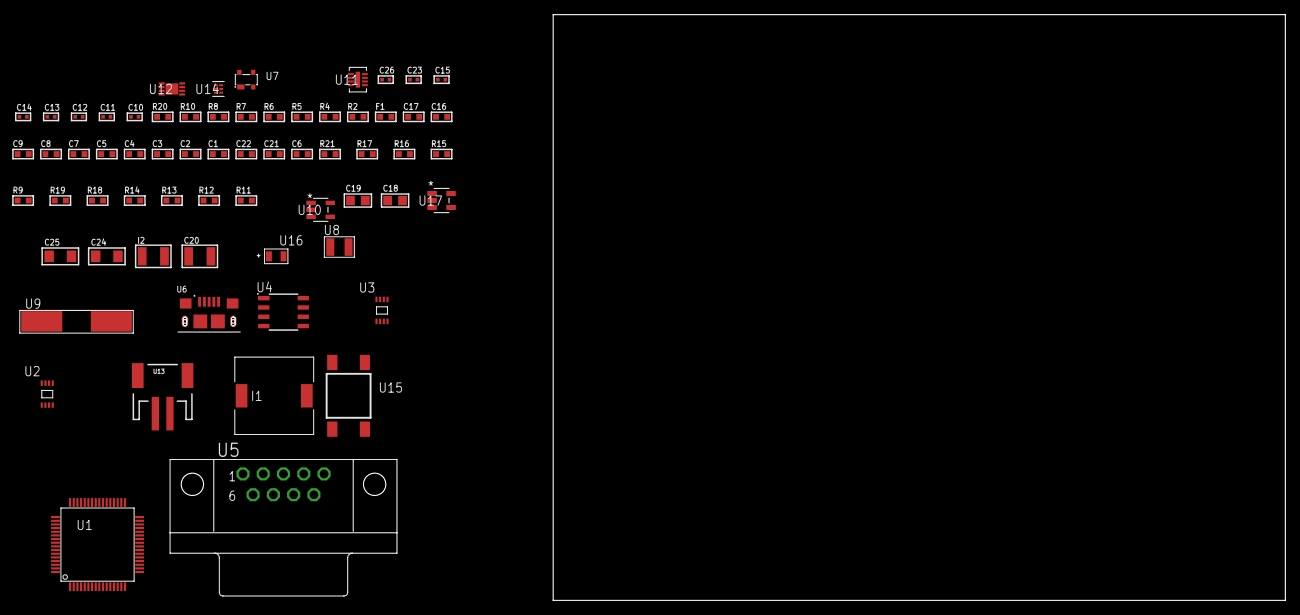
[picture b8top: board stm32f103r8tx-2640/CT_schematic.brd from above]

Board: 2 copper layers, 65 parts (0 on the bottom side), 37 nets, no tracks yet.

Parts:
C1, C9, C16, C17: 1e-06; C0603
C2, C3, C4, C5, C7: 1e-07; C0603
C6: 4.7e-06; C0603
C8: 1e-08; C0603
C10, C11, C12, C13: 1e-11; C0402
C14, C15, C26: 1e-08; C0402
C18, C19: 1e-05; C0805
C20: 1e-05; C1210
C21: 2.2e-06; C0603
C22: 2.2e-07; C0603
C23: 1e-07; C0402
C24, C25: 1e-05; C1206
F1: 240.0; L0603
I1: 5.2e-06; DR1040
I2: 1e-05; L1210
R2: 1000.0; R0603
R4: 4700.0; R0603
R5, R6, R7, R8: 2200.0; R0603
R9, R15, R16, R21: 10000.0; R0603
R10: 120.0; R0603
R11: 309473.68421053; R0603
R12: 1000000.0; R0603
R13: 100000.0; R0603
R14: 560000.0; R0603
R17: 18000.0; R0603
R18: 470000.0; R0603
R19: 120000.0; R0603
R20: 2000.0; R0603
U1: stm32f103r8t7; LQFP64
U2: 24AA00T-I/MNY; TDFN-8/6MM
U3: 24AA02T-I/MNY; TDFN-8/6MM
U4: MCP2562-E/SN; SOIC-8
U5: 182-009-113R531; 182-009-MALE
U6: 10118193-0001LF; FCI_10118193-0001LF
U7: prtr5v0u2ax; SOT143B
U8: ABS07-32.768KHZ-7-T
U9: ABLS-25.000MHZ-B2F-T
U10: ltc3406es5; TSOT-23-5
U11: LT3494AEDDB#TRMPBF; DFN-8_DDB
U12: MCP73831T-2ACI/MC; DFN8_2X3MC
U13: S2B-PH-SM4-TB(LF)(SN); JST-2-SMD
U14: TPS3895ADRYR; SON-6
U15: 4-1437565-2; SW_4-1437565-2
U16: Q65110A2395; LGM67K-G1J2-24-Z
U17: nc7sz125m5x; NC7SZ125M5X

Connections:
CLK_CRYSTAL_U1_3: C10.1, U1.3, U8.1
CLK_CRYSTAL_U1_4: C11.1, U1.4, U8.2
CLK_CRYSTAL_U1_5: C12.1, U1.5, U9.1
CLK_CRYSTAL_U1_6: C13.1, U1.6, U9.2
GND: C1.2, C2.2, C3.2, C4.2, C5.2, C6.2, C7.2, C8.2, C9.2, C10.2, C11.2, C12.2, C13.2, C14.2, C15.2, C16.2, C17.2, C18.2, C19.1, C19.2, C20.2, C21.2, C22.2, C23.2, C24.2, C25.2, C26.2, R2.2, R9.2, R11.2, R17.2, R19.2, R20.2, U1.12, U1.18, U1.31, U1.47, U1.63, U2.4, U3.4, U3.7, U4.2, U4.8, U5.5, U6.5, U6.6, U6.7, U6.8, U6.9, U7.1, U10.2, U11.2, U11.9, U12.6, U12.9, U13.2, U14.2, U16.C, U17.1, U17.3
INPUT_USBPOWER_5V: C24.1, R21.2, U6.1, U7.4, U12.1, U12.2
NET_U1_7: R4.1, U1.7, U17.4
NET_U1_13: C8.1, C9.1, F1.1, U1.13
NET_U1_29: R7.1, U1.29, U2.6
NET_U1_30: R8.1, U1.30, U2.5
NET_U1_57: U15.3, U15.4
NET_U1_58: R5.1, U1.58, U3.6
NET_U1_59: R6.1, U1.59, U3.5
NET_U1_60: R9.1, U1.60
NET_U4_6: R10.2, U4.6
NET_U5_2: R10.2, U4.6, U5.2
NET_U5_3: R10.1, U4.7, U5.3
NET_U10_3: I1.1, U10.3
NET_U10_5: R11.1, R12.1, U10.5
NET_U10_ATNET_3: I1.2, R12.2
NET_U11_1: I2.1, U11.1
NET_U11_5: R13.1, U11.5
NET_U11_6: R14.1, U11.6
NET_U11_8: C22.1, U11.8
NET_U12_5: R21.1, U12.5
NET_U12_8: R20.1, U12.8
NET_U14_1: R16.1, R17.1, U14.1
NET_U14_3: R18.2, R19.1, U14.3
NET_U14_4: R15.1, U14.4, U17.2
NET_U15_1: R2.1, U15.1, U15.2
PROC_CAN_RX: U1.61, U4.4
PROC_CAN_TX: U1.62, U4.1
PROC_USB_DM: U1.44, U6.2, U7.3
PROC_USB_DP: U1.45, U6.3, U7.2
VCC_S1_3V7: C18.1, C20.1, C25.1, I2.2, R13.2, U10.4, U11.3, U11.4, U12.3, U12.4, U13.1
VCC_TIER1_2V5: C1.1, C2.1, C3.1, C4.1, C5.1, C6.1, C7.1, C14.1, C15.1, C17.1, C19.2, C23.1, C26.1, F1.2, I1.2, R4.2, R5.2, R6.2, R7.2, R8.2, R12.2, R15.2, R16.2, R18.1, U1.1, U1.19, U1.32, U1.48, U1.64, U2.8, U3.8, U4.5, U14.6, U17.5
VCC_TIER1_5V0: C16.1, C21.1, R14.2, U4.3, U11.7
